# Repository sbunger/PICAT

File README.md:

# PICAT
PiCat is a custom devboard created with help from HackClub! The board is completely custom, running on an RP2040 and is connected to 16MB of flash memory and two 5mm LEDs that can be controlled. PCBs were created in KICAD and renders were created using Blender (renders have out of date silkscreen, but should otherwise be identical to the pcb).

I created this project gain experience working on PCBs while creating a product I will use. I plan to use at least one of the two devboards as an LED controller in a 3d printed lamp, and the other one will be used for a future project. 

The devboard can be controlled through circuitpython and arduino. Right now, I am using circuitpython to make two LEDs blink (example file in code folder).

## Photos!

## PCB and Schematics
PCBs were created competely by hand in KICAD.

## Renders

## BOM
| Product Name | Link | Quantity | Total Cost (Tax Included) | 
| - | - | - | - |
| JLCPCB | <a href="https://jlcpcb.com/">https://jlcpcb.com/</a> | 5x PCB, 2x PCBA | $55.63 |
| 3x1 Pin Headers (Male) | <a href="https://www.aliexpress.us/item/3256806916819038.html">https://www.aliexpress.us/item/3256806916819038.html</a> | 1 Lot (10pc) | $2.93 |
| 20x1 Pin Headers (Male) | <a href="https://www.aliexpress.us/item/2255800867206912.html">https://www.aliexpress.us/item/2255800867206912.html</a> | 1 Lot (20pc) | $2.74 |
| - | - | Total Cost: | $61.3 (US) |

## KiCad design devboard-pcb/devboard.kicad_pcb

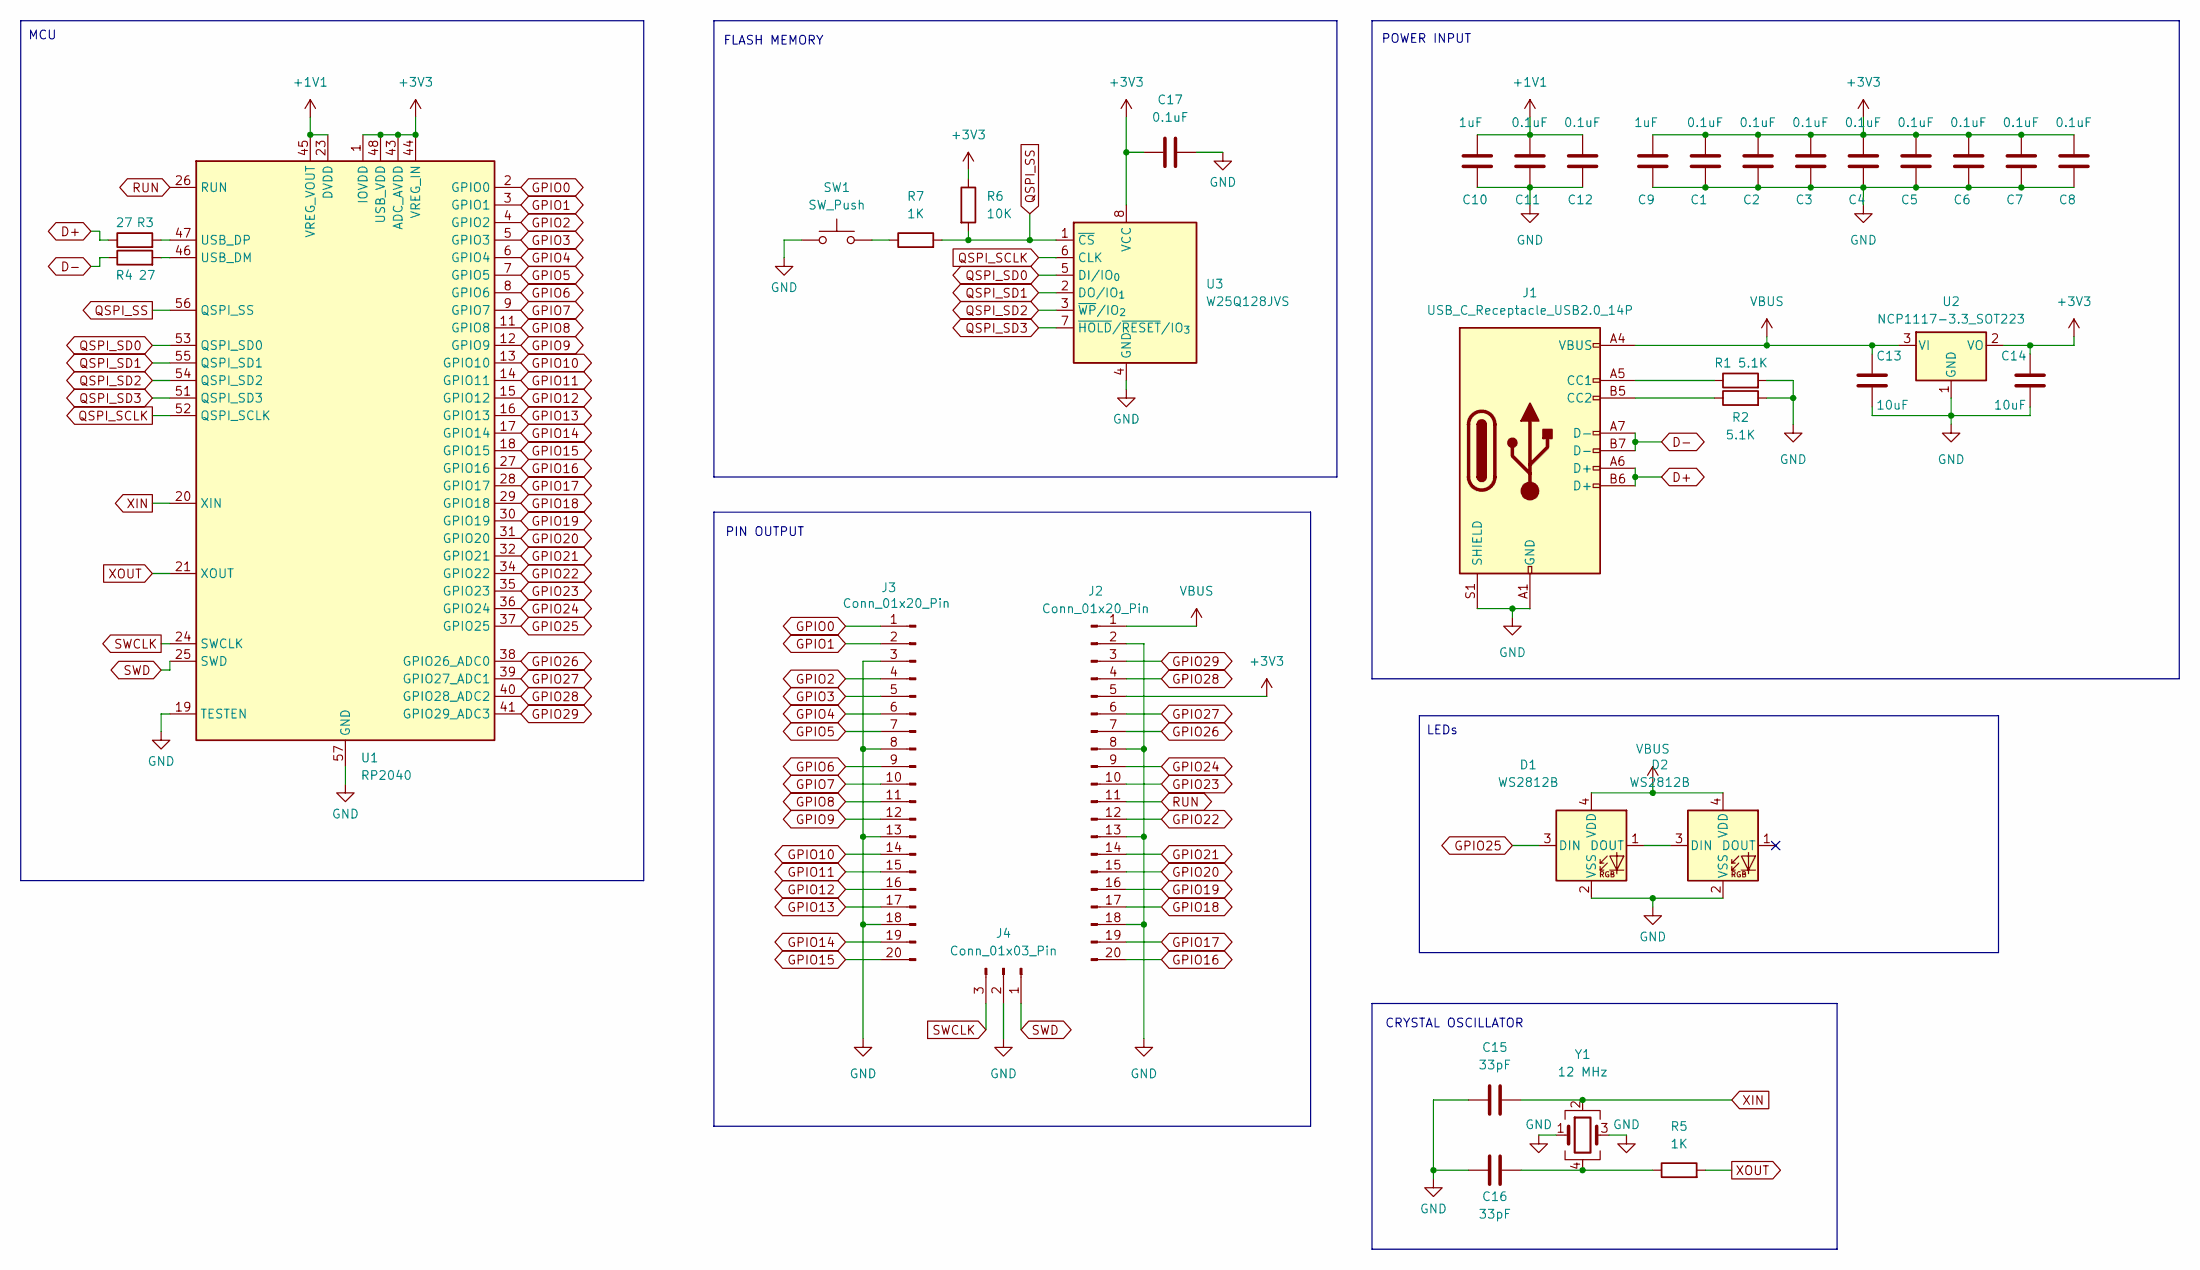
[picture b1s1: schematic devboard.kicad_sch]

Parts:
C1, C2, C3, C4, C5, C6, C7, C8, C11, C12, C17: 0.1uF; C_0402_1005Metric
C9, C10: 1uF; C_0402_1005Metric
C13, C14: 10uF; C_0603_1608Metric
C15, C16: 33pF; C_0402_1005Metric
D1, D2: WS2812B; LED_WS2812B-2020_PLCC4_2.0x2.0mm
J1: USB_C_Receptacle_USB2.0_14P; USB_C_Receptacle_HRO_TYPE-C-31-M-12
J2, J3: Conn_01x20_Pin; PinHeader_1x20_P2.54mm_Vertical
J4: Conn_01x03_Pin; PinHeader_1x03_P2.54mm_Vertical
R1, R2: 5.1K; R_0402_1005Metric
R3, R4: 27; R_0402_1005Metric
R5, R7: 1K; R_0402_1005Metric
R6: 10K; R_0402_1005Metric
SW1: SW_Push; SW_Push_SPST_NO_Alps_SKRK
U1: RP2040; QFN-56-1EP_7x7mm_P0.4mm_EP3.2x3.2mm
U2: NCP1117-3.3_SOT223; SOT-23
U3: W25Q128JVS; Winbond_USON-8-1EP_3x2mm_P0.5mm_EP0.2x1.6mm
Y1: 12 MHz; Crystal_SMD_3225-4Pin_3.2x2.5mm

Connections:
+1V1: C10.1, C11.1, C12.1, U1.23 (DVDD), U1.45 (VREG_VOUT), U1.50 (DVDD)
+3V3: C1.1, C2.1, C3.1, C4.1, C5.1, C6.1, C7.1, C8.1, C9.1, C14.1, C17.1, J2.5, R6.1, U1.1 (IOVDD), U1.10 (IOVDD), U1.22 (IOVDD), U1.33 (IOVDD), U1.42 (IOVDD), U1.43 (ADC_AVDD), U1.44 (VREG_IN), U1.48 (USB_VDD), U1.49 (IOVDD), U2.2 (VO), U3.8 (VCC)
D+: J1.A6 (D+), J1.B6 (D+), R3.1
D-: J1.A7 (D-), J1.B7 (D-), R4.1
GND: C1.2, C2.2, C3.2, C4.2, C5.2, C6.2, C7.2, C8.2, C9.2, C10.2, C11.2, C12.2, C13.2, C14.2, C15.1, C16.1, C17.2, D1.2 (VSS), D2.2 (VSS), J1.A1 (GND), J1.A12 (GND), J1.B1 (GND), J1.B12 (GND), J1.S1 (SHIELD), J2.2, J2.8, J2.13, J2.18, J3.3, J3.8, J3.13, J3.18, J4.2, R1.2, R2.2, SW1.1, U1.19 (TESTEN), U1.57 (GND), U2.1 (GND), U3.4 (GND), Y1.1, Y1.3
GPIO0: J3.1, U1.2 (GPIO0)
GPIO1: J3.2, U1.3 (GPIO1)
GPIO2: J3.4, U1.4 (GPIO2)
GPIO3: J3.5, U1.5 (GPIO3)
GPIO4: J3.6, U1.6 (GPIO4)
GPIO5: J3.7, U1.7 (GPIO5)
GPIO6: J3.9, U1.8 (GPIO6)
GPIO7: J3.10, U1.9 (GPIO7)
GPIO8: J3.11, U1.11 (GPIO8)
GPIO9: J3.12, U1.12 (GPIO9)
GPIO10: J3.14, U1.13 (GPIO10)
GPIO11: J3.15, U1.14 (GPIO11)
GPIO12: J3.16, U1.15 (GPIO12)
GPIO13: J3.17, U1.16 (GPIO13)
GPIO14: J3.19, U1.17 (GPIO14)
GPIO15: J3.20, U1.18 (GPIO15)
GPIO16: J2.20, U1.27 (GPIO16)
GPIO17: J2.19, U1.28 (GPIO17)
GPIO18: J2.17, U1.29 (GPIO18)
GPIO19: J2.16, U1.30 (GPIO19)
GPIO20: J2.15, U1.31 (GPIO20)
GPIO21: J2.14, U1.32 (GPIO21)
GPIO22: J2.12, U1.34 (GPIO22)
GPIO23: J2.10, U1.35 (GPIO23)
GPIO24: J2.9, U1.36 (GPIO24)
GPIO25: D1.3 (DIN), U1.37 (GPIO25)
GPIO26: J2.7, U1.38 (GPIO26_ADC0)
GPIO27: J2.6, U1.39 (GPIO27_ADC1)
GPIO28: J2.4, U1.40 (GPIO28_ADC2)
GPIO29: J2.3, U1.41 (GPIO29_ADC3)
unnamed: C16.2, R5.1, Y1.4
unnamed: D1.1 (DOUT), D2.3 (DIN)
unnamed: J1.A5 (CC1), R1.1
unnamed: J1.B5 (CC2), R2.1
unnamed: R7.1, SW1.2
unnamed: R4.2, U1.46 (USB_DM)
unnamed: R3.2, U1.47 (USB_DP)
QSPI_SCLK: U1.52 (QSPI_SCLK), U3.6 (CLK)
QSPI_SD0: U1.53 (QSPI_SD0), U3.5 (DI/IO_{0})
QSPI_SD1: U1.55 (QSPI_SD1), U3.2 (DO/IO_{1})
QSPI_SD2: U1.54 (QSPI_SD2), U3.3 (~WP/IO_{2})
QSPI_SD3: U1.51 (QSPI_SD3), U3.7 (~HOLD/~RESET/IO_{3})
QSPI_SS: R6.2, R7.2, U1.56 (QSPI_SS), U3.1 (~CS)
RUN: J2.11, U1.26 (RUN)
SWCLK: J4.3, U1.24 (SWCLK)
SWD: J4.1, U1.25 (SWD)
VBUS: C13.1, D1.4 (VDD), D2.4 (VDD), J1.A4 (VBUS), J1.A9 (VBUS), J1.B4 (VBUS), J1.B9 (VBUS), J2.1, U2.3 (VI)
XIN: C15.2, U1.20 (XIN), Y1.2
XOUT: R5.2, U1.21 (XOUT)

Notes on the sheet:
POWER INPUT
FLASH MEMORY
PIN OUTPUT
MCU
LEDs
CRYSTAL OSCILLATOR

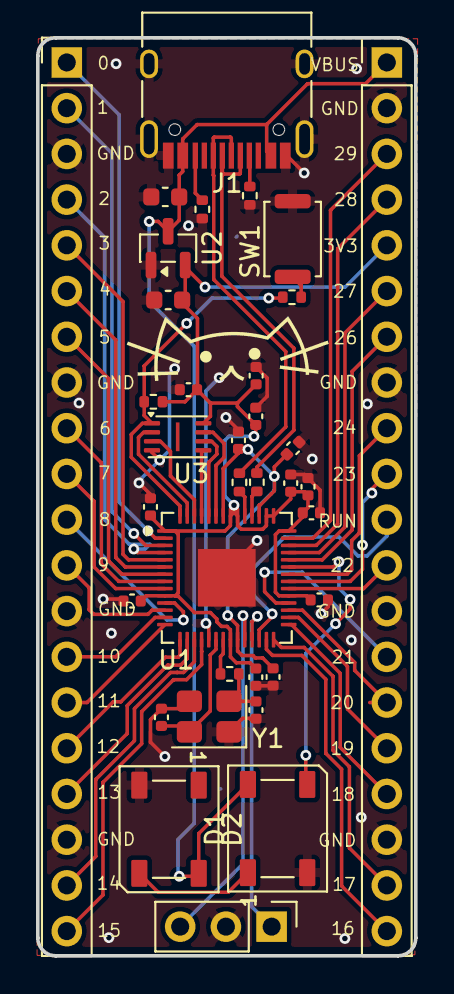
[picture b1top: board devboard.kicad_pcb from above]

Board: 2 copper layers, 21.0 x 51.0 mm, 35 parts (0 on the bottom side), 54 nets.

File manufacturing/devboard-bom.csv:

Id,Designator,Footprint,Quantity,Comment,Supplier and ref
1,"D2,D1",LED_WS2812B_PLCC4_5.0x5.0mm_P3.2mm,2,WS2812B,
2,U1,QFN-56-1EP_7x7mm_P0.4mm_EP3.2x3.2mm,1,RP2040,
3,"C10,C9",C_0402_1005Metric,2,1uF,
4,"R5,R7",R_0402_1005Metric,2,1K,
5,"C4,C11,C8,C1,C3,C7,C5,C6,C17,C2,C12",C_0402_1005Metric,11,0.1uF,
6,U2,SOT-23,1,NCP1117-3.3_SOT223,
7,"R2,R1",R_0402_1005Metric,2,5.1K,
8,Y1,Crystal_SMD_3225-4Pin_3.2x2.5mm_MOD,1,12 MHz,
9,U3,Winbond_USON-8-1EP_3x2mm_P0.5mm_EP0.2x1.6mm,1,W25Q128JVS,
10,SW1,SW_Push_SPST_NO_Alps_SKRK,1,SW_Push,
11,"R4,R3",R_0402_1005Metric,2,27,
12,"C16,C15",C_0402_1005Metric,2,33pF,
13,J1,USB_C_Receptacle_HRO_TYPE-C-31-M-12,1,USB_C_Receptacle_USB2.0_14P,
14,R6,R_0402_1005Metric,1,10K,
15,"C14,C13",C_0603_1608Metric,2,10uF,
16,J4,PinHeader_1x03_P2.54mm_Vertical,1,Conn_01x03_Pin,
17,"J2,J3",PinHeader_1x20_P2.54mm_Vertical,2,Conn_01x20_Pin,

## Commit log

2025-12-14 Uploaded All Files
2025-12-14 Update README.md to Final
2025-12-15 Updated Renders, blend file
2025-12-16 Blender file added
2026-01-02 Added test script
2026-01-02 Added images
2026-01-02 Add photos section to README
    Added a new section for project photos in the README.
2026-01-02 Update README with control methods for devboard
    Added information about controlling the devboard with CircuitPython and Arduino.
2026-01-03 Fix image tag for IMG_2569.jpeg in README
